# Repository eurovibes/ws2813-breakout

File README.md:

<!-- SPDX-FileCopyrightText: 2021 Benedikt Spranger <b.spranger@linutronix.de> -->
<!-- SPDX-License-Identifier: CERN-OHL-S-2.0 -->

# ws2318-breakout - A ws2813 LED breakout board

## License rules

ws2318-breakout is provided under the terms of the CERN-OHL-S license version 2
as provided in the LICENSES/CERN-OHL-S-2.0 file.

Instead of adding license boilerplates to the individual files, ws2318-breakout
uses SPDX license identifiers, which are machine parseable and considered
legaly equivalent.

The SPDX license identifier in ws2318-breakout shall be added at the first
possible line in a file which can contain a comment. This is normally the
first line except for scripts. Scripts require the #!PATH_TO_INTERPRETER tag
in the first line; place the SPDX identifier into the second line.

The SPDX license identifier is added in form of a comment.

## Copyright and License

> Copyright Benedikt Spranger 2021.
> This source describes Open Hardware and is licensed under the CERNOHL-S v2.
> You may redistribute and modify this source and make products using it
> under the terms of the CERN-OHL-S v2 (https://ohwr.org/cern ohl s v2.txt).
> This source is distributed WITHOUT ANY EXPRESS OR IMPLIED WARRANTY, INCLUDING
> OF MERCHANTABILITY, SATISFACTORY QUALITY AND FITNESS FOR A PARTICULAR PURPOSE.
> Please see the CERN-OHL-S v2 for applicable conditions.
> Source location: https://github.com/eurovibes/ws2318-breakout
> As per CERN-OHL-S v2 section 4, should You produce hardware based
> on this source, You must where practicable maintain the Source Location
> visible on the external case of the ws2318-breakout or other products you make
> using this source.

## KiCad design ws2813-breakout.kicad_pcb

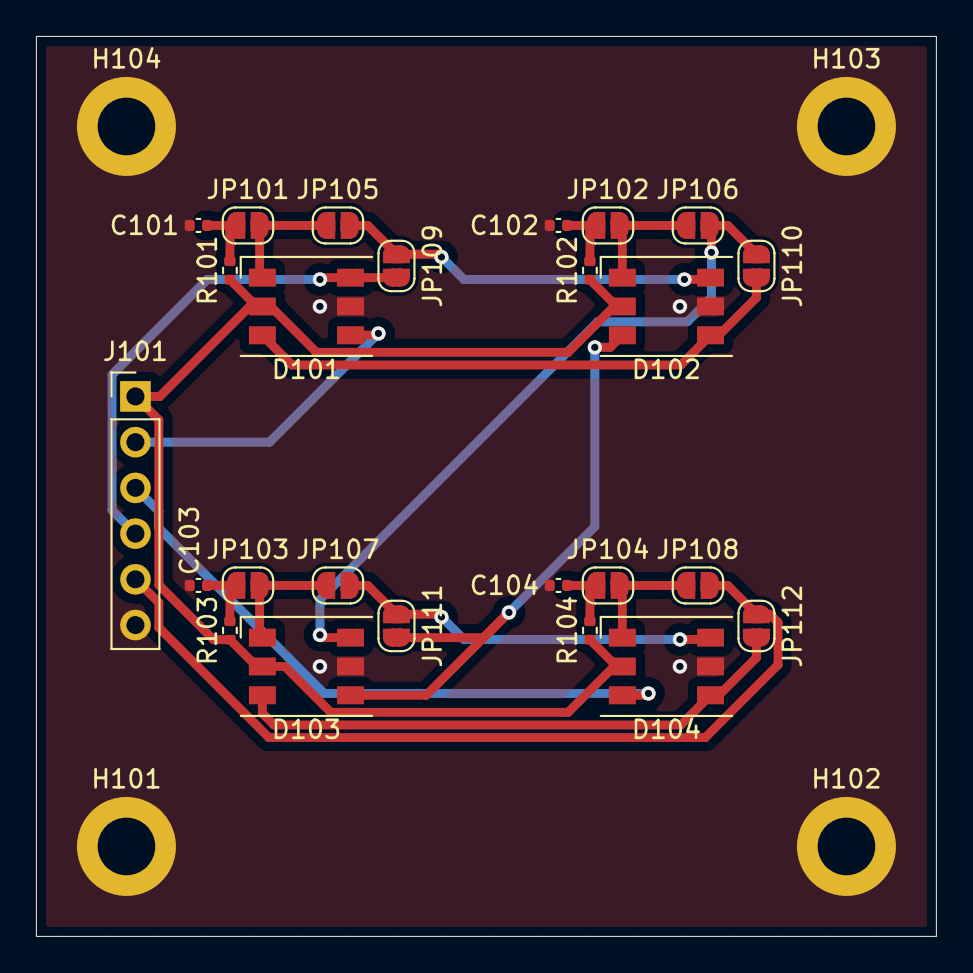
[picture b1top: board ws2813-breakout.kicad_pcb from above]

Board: 2 copper layers, 50.0 x 50.0 mm, 29 parts (0 on the bottom side), 20 nets.

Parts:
C101, C102, C103, C104: 100n; C_0402_1005Metric
D101, D102, D103, D104: WS2813; LED_WS2812_PLCC6_5.0x5.0mm_P1.6mm
H101, H102, H103, H104: MountingHole_3.2mm_M3_ISO14580_Pad
J101: Breakout; PinHeader_1x06_P2.54mm_Vertical
JP101, JP102, JP103, JP104: RC; SolderJumper-2_P1.3mm_Open_RoundedPad1.0x1.5mm
JP105, JP106, JP107, JP108: B-B; SolderJumper-2_P1.3mm_Open_RoundedPad1.0x1.5mm
JP109, JP110, JP111, JP112: bypass; SolderJumper-2_P1.3mm_Open_RoundedPad1.0x1.5mm
R101, R102, R103, R104: 150; R_0402_1005Metric

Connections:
+5V: D101.2, D102.2, D103.2, D104.2, J101.1, R101.1, R102.1, R103.1, R104.1
/BI: D101.6, J101.4, JP109.2
/BO: J101.5, JP108.2, JP112.1
/DI: D101.4, J101.2
/DO: D104.3, J101.3
GND: C101.1, C102.1, C103.1, C104.1, D101.5, D102.5, D103.5, D104.5, H101.1, H102.1, H103.1, H104.1, J101.6
unnamed: C101.2, JP101.1, R101.2
unnamed: C102.2, JP102.1, R102.2
unnamed: C103.2, JP103.1, R103.2
unnamed: C104.2, JP104.1, R104.2
unnamed: D101.1, JP101.2, JP105.1
unnamed: D101.3, D102.4, JP110.2
unnamed: D102.1, JP102.2, JP106.1
unnamed: D102.3, D103.4, JP111.2
unnamed: D102.6, JP105.2, JP109.1
unnamed: D103.1, JP103.2, JP107.1
unnamed: D103.3, D104.4, JP112.2
unnamed: D103.6, JP106.2, JP110.1
unnamed: D104.1, JP104.2, JP108.1
unnamed: D104.6, JP107.2, JP111.1

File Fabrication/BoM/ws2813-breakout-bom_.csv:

Row,Referencias,Parte,Valor,P/N,Fabricante,Cod. Digi-Key,Footprint,Descripción,Quantity Per PCB
1,C101 C102 C103 C104,C,100 nF,,,,C_0402_1005Metric,,4
2,D101 D102 D103 D104,WS2813,WS2813,,,,LED_WS2812_PLCC6_5.0x5.0mm_P1.6mm,,4
3,H101 H102 H103 H104,MountingHole_Pad,~,,,,MountingHole_3.2mm_M3_ISO14580_Pad,,4
4,J101,Conn_01x06,Breakout,,,,PinHeader_1x06_P2.54mm_Vertical,,1
5,JP101 JP102 JP103 JP104 JP105 JP106 JP107 JP108 JP109 JP110 JP111 JP112,SolderJumper_2_Open,RC,,,,SolderJumper-2_P1.3mm_Open_RoundedPad1.0x1.5mm,,12
6,R101 R102 R103 R104,R,150 Ω,,,,R_0402_1005Metric,,4





Project info:
Schematic:,ws2813-breakout
Variant:,default
Revision:,
Date:,2021-09-26_18-59-48
KiCad Version:,5.1.9+dfsg1-1~bpo10+1
Statistics:
Component Groups:,6
Component Count:,29
Fitted Components:,29
Number of PCBs:,1
Total Components:,29

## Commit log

2021-09-26 Deploying to gh-pages from @ eurovibes/ws2813-breakout@6b79f92d6da312739703d27101520cba4547b18c 🚀
2021-09-26 Initial gh-pages commit
2021-09-26 Deploying to gh-pages from @ eurovibes/ws2813-breakout@70aee180076696aa3aaede84f0b52b7f4eeace9b 🚀
2021-09-26 Deploying to gh-pages from @ eurovibes/ws2813-breakout@222054f638ec0c147aa3256b68fdbb6903eb7900 🚀
